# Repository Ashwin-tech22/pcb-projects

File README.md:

# pcb-projects
I have made PCB design using kicad version 9

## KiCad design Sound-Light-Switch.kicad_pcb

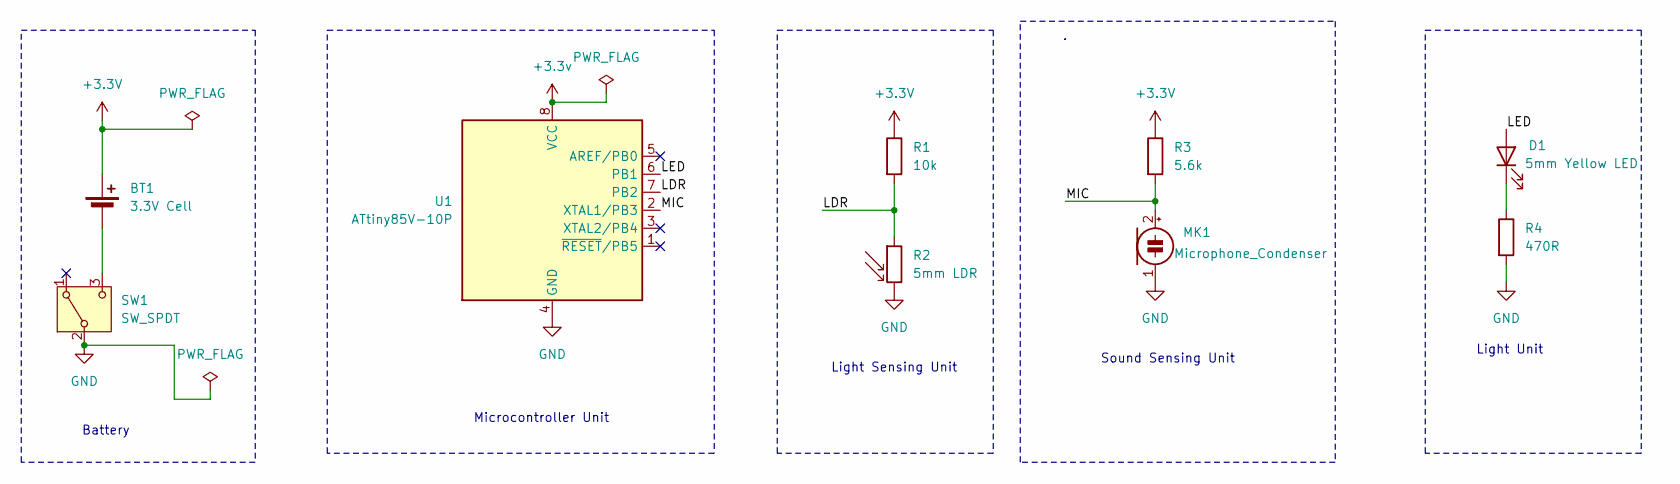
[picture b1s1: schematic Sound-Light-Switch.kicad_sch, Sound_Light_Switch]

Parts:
BT1: 3.3V Cell; BatteryHolder_ComfortableElectronic_CH273-2450_1x2450
D1: 5mm Yellow LED; LED_D5.0mm
MK1: Microphone_Condenser; PinHeader_1x02_P2.54mm_Vertical
R1: 10k; R_Axial_DIN0207_L6.3mm_D2.5mm_P15.24mm_Horizontal
R2: 5mm LDR; R_LDR_5.1x4.3mm_P3.4mm_Vertical
R3: 5.6k; R_Axial_DIN0207_L6.3mm_D2.5mm_P15.24mm_Horizontal
R4: 470R; R_Axial_DIN0207_L6.3mm_D2.5mm_P15.24mm_Horizontal
SW1: SW_SPDT; SW_Slide_SPDT_Angled_CK_OS102011MA1Q
U1: ATtiny85V-10P; DIP-8_W7.62mm

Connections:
+3.3V: BT1.1 (+), R1.1, R3.1
+3.3v: U1.8 (VCC)
/LDR: R1.2, R2.1, U1.7 (PB2)
/LED: D1.2 (A), U1.6 (PB1)
/MIC: MK1.2 (+), R3.2, U1.2 (XTAL1/PB3)
GND: MK1.1 (-), R2.2, R4.2, SW1.2 (B), U1.4 (GND)
unnamed: BT1.2 (-), SW1.3 (C)
unnamed: D1.1 (K), R4.1

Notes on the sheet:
Sound Sensing Unit
Light Unit
Light Sensing Unit
Battery
Microcontroller Unit

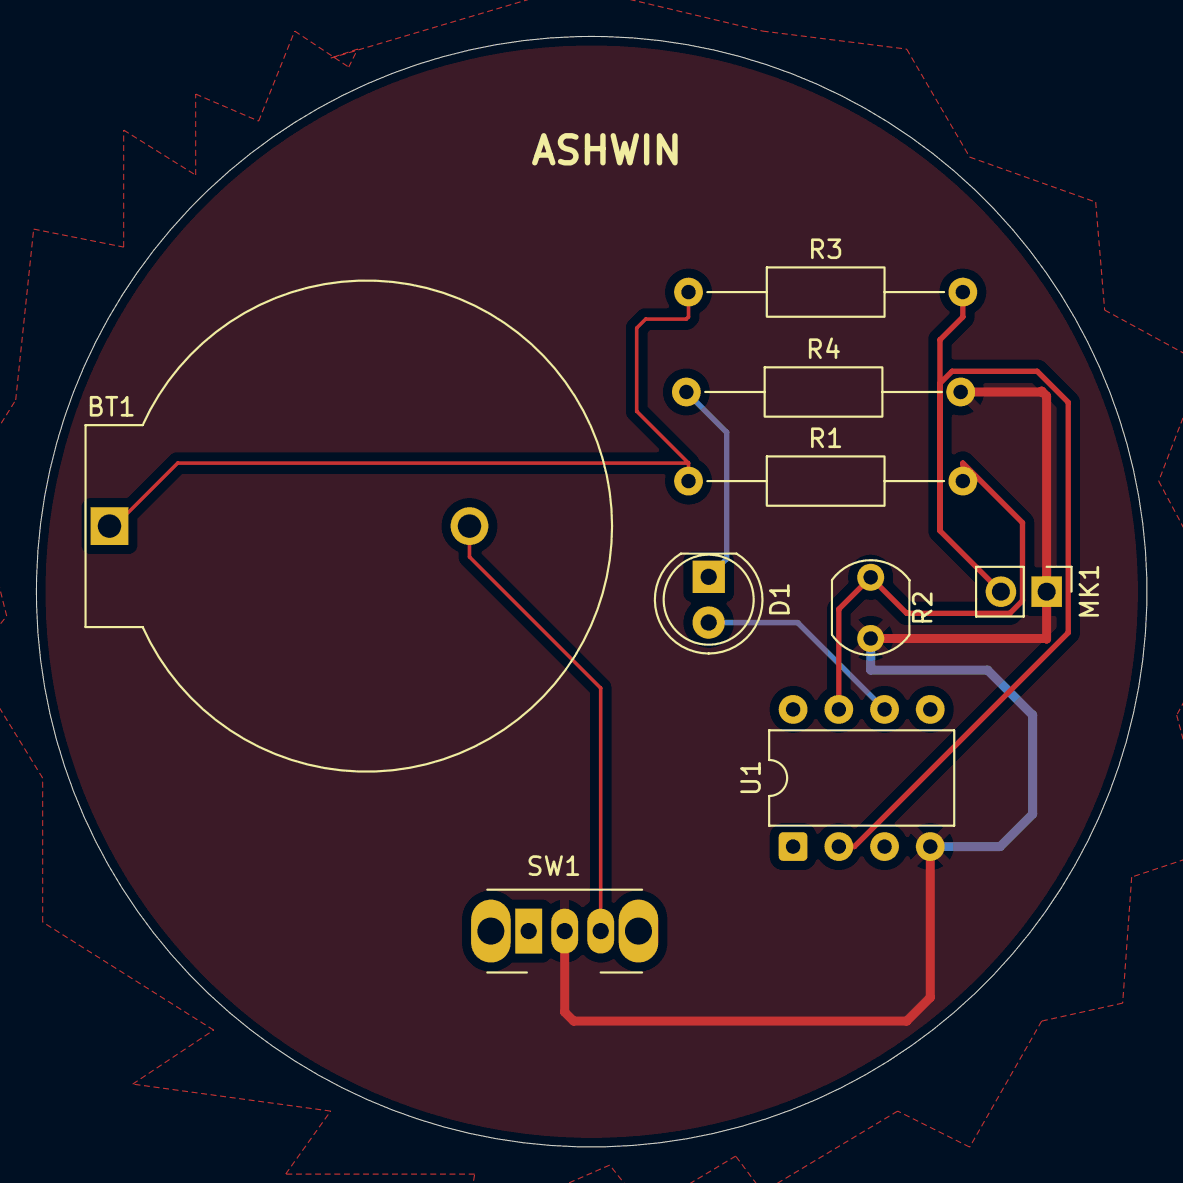
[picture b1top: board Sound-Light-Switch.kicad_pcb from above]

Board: 2 copper layers, 61.7 x 61.7 mm, 9 parts (0 on the bottom side), 7 nets.
